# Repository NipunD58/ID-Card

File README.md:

# ID-Card
Made for an event in my school, nothing much, just a simple LED chaser made with 555 timer IC and CD4017BE IC.

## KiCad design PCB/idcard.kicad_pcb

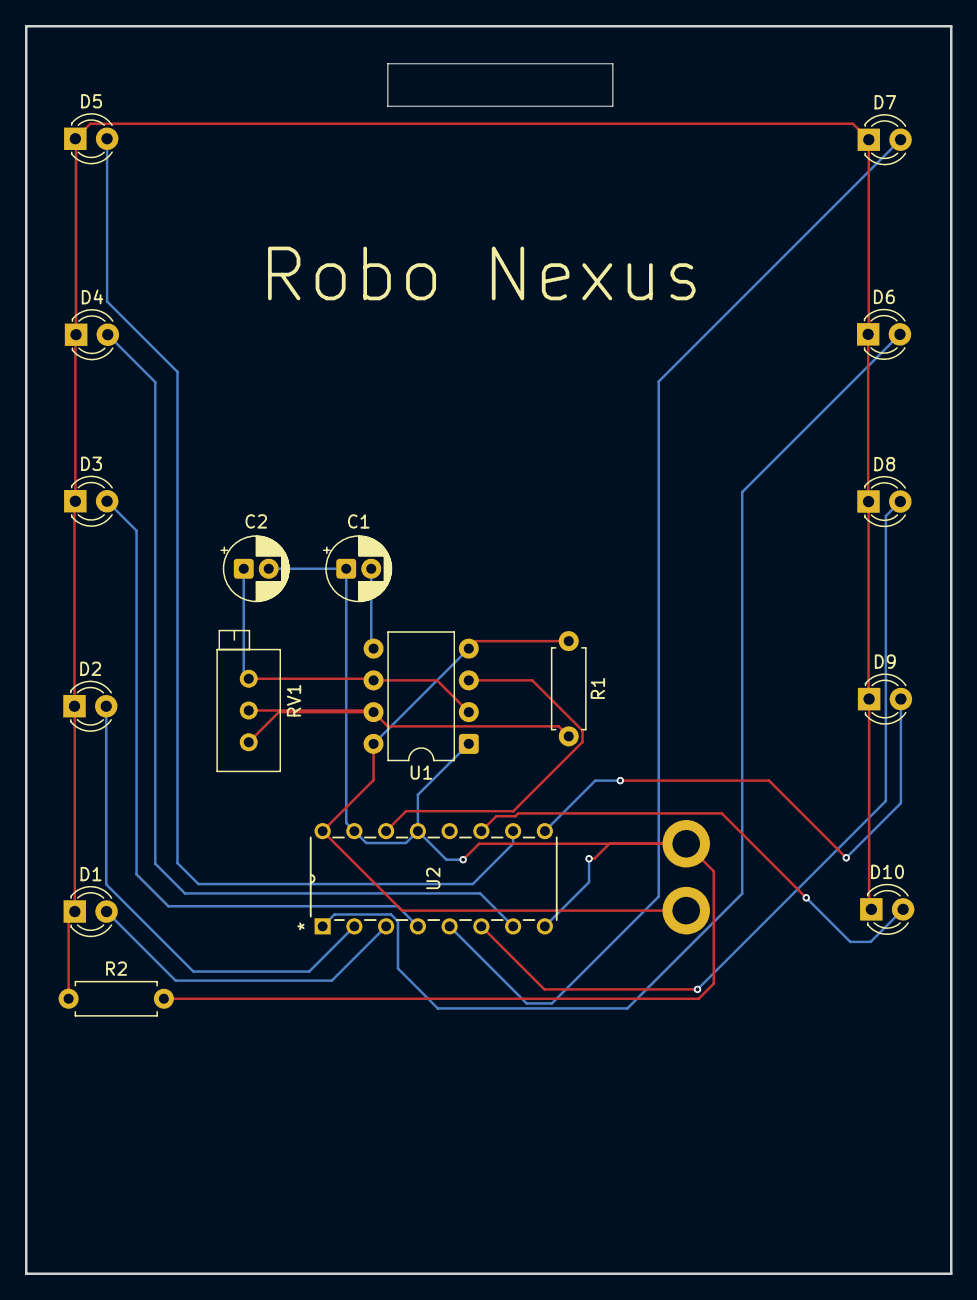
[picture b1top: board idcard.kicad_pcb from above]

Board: 2 copper layers, 74.0 x 99.8 mm, 19 parts (0 on the bottom side), 17 nets.

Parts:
C1: 0.01uf; CP_Radial_D5.0mm_P2.00mm
C2: 1uF; CP_Radial_D5.0mm_P2.00mm
D1, D2, D3, D4, D5, D6, D7, D8, D9, D10: LED; LED_D3.0mm
H1: Gnd; MountingHole_2.2mm_M2_DIN965_Pad
H2: +5V; MountingHole_2.2mm_M2_DIN965_Pad
R1: 1K; R_Axial_DIN0207_L6.3mm_D2.5mm_P7.62mm_Horizontal
R2: 470; R_Axial_DIN0207_L6.3mm_D2.5mm_P7.62mm_Horizontal
RV1: 50K; Potentiometer_Bourns_3296X_Horizontal
U1: NE555P; DIP-8_W7.62mm
U2: 4017; N16

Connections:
+5V: H2.1, R1.1, U1.4 (R), U1.8 (VCC), U2.16 (VDD)
GND: C1.1, C2.2, H1.1, R2.2, U1.1 (GND), U2.8 (VSS), U2.13 (CKEN), U2.15 (Reset)
unnamed: D1.2 (A), U2.3 (Q0)
unnamed: D1.1 (K), D2.1 (K), D3.1 (K), D4.1 (K), D5.1 (K), D6.1 (K), D7.1 (K), D8.1 (K), D9.1 (K), D10.1 (K), R2.1
unnamed: D2.2 (A), U2.2 (Q1)
unnamed: D3.2 (A), U2.4 (Q2)
unnamed: D4.2 (A), U2.7 (Q3)
unnamed: D5.2 (A), U2.10 (Q4)
unnamed: D6.2 (A), U2.1 (Q5)
unnamed: D7.2 (A), U2.5 (Q6)
unnamed: D8.2 (A), U2.6 (Q7)
unnamed: D9.2 (A), U2.9 (Q8)
unnamed: D10.2 (A), U2.11 (Q9)
unnamed: C1.2, U1.5 (CV)
unnamed: R1.2, RV1.1, RV1.2, U1.7 (DIS)
OUT: U1.3 (Q), U2.14 (CLK)
TR: C2.1, RV1.3, U1.2 (TR), U1.6 (THR)
